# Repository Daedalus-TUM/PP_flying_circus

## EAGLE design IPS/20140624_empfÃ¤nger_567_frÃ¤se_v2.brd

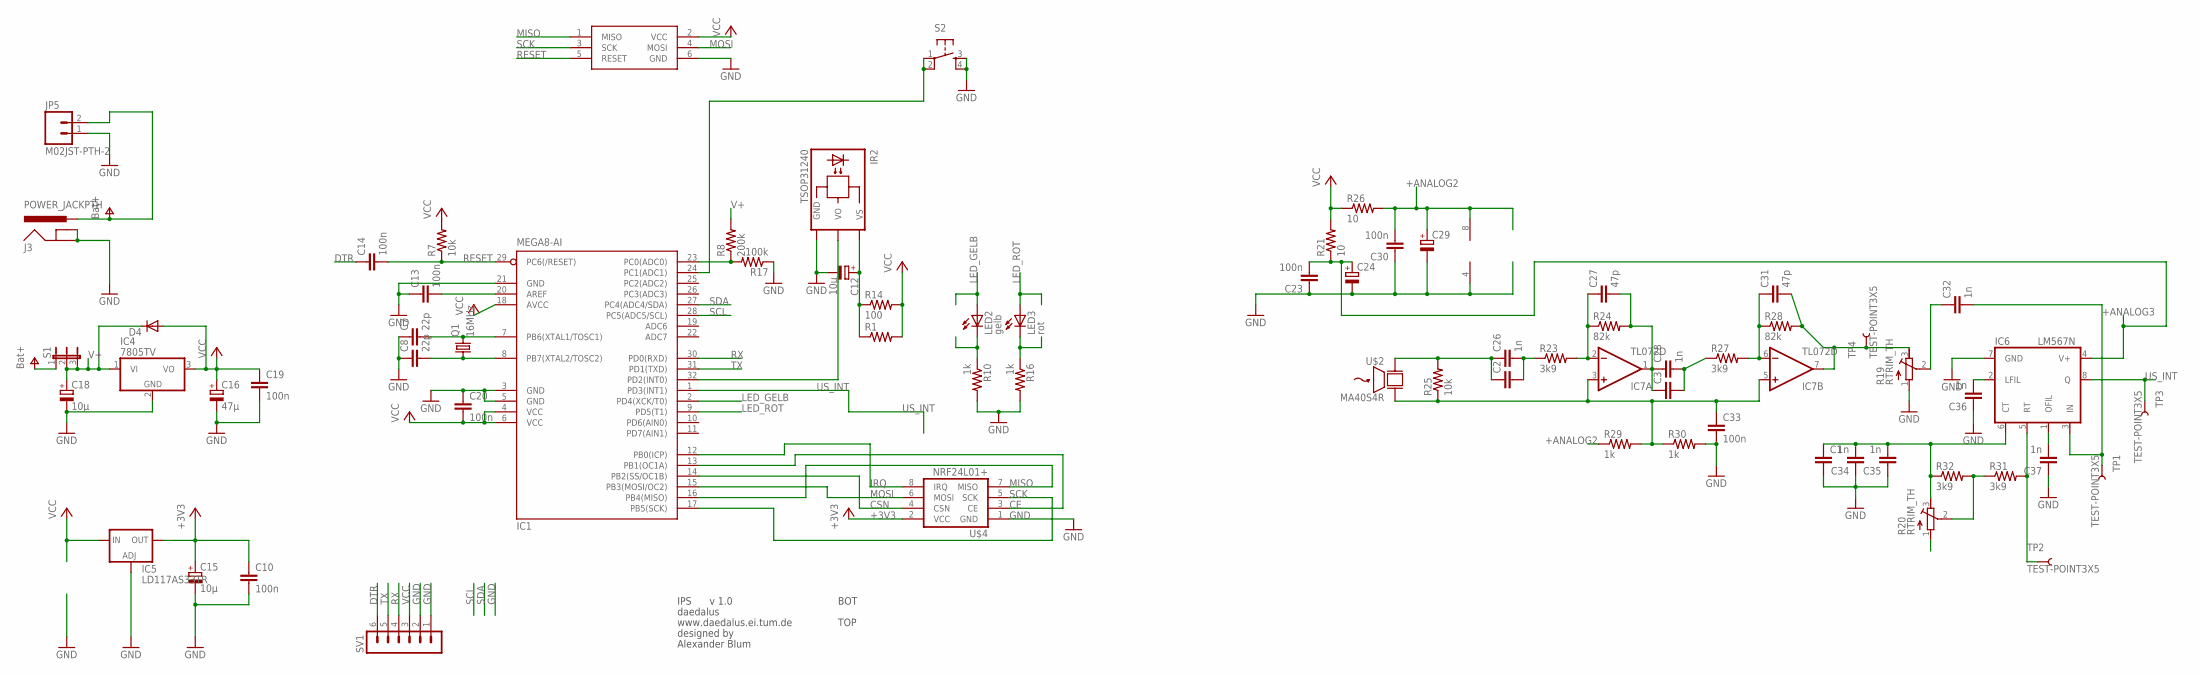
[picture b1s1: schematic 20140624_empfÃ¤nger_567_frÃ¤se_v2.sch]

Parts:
C1, C2, C3: CAP1206; 1206
C7, C8: 22p; 0805
C10, C13, C14, C19, C20, C23, C30, C33: 100n; 0805
C12, C15, C18: 10µ; E2,5-5
C16: 47µ; E2,5-5
C24, C29: CPOL-EUE2.5-5; E2,5-5
C26, C28, C32, C34, C35, C36, C37: 1n; 0805
C27, C31: 47p; 0805
D4: DIODE-MINIMELF; MINIMELF
IC1: MEGA8-AI; TQFP32-08
IC4: 7805TV; TO220V
IC5: LD117AS33TR; SOT223
IC6: LM567N; DIL08
IC7: TL072D; SO08
IR2: TSOP31240
J3: POWER_JACKPTH; POWER_JACK_PTH
JP5: M02JST-PTH-2; JST-2-PTH
LED2: gelb; LED5MM
LED3: rot; LED5MM
Q1: 16MHz; HC49/S
R1: RESISTOR1206; 1206
R7, R25: 10k; 0805
R8: 200k; 0805
R10, R16, R29, R30: 1k; 0805
R14: 100; 0805
R17: 100k; 0805
R19, R20: RTRIM_TH
R21, R26: 10; 0805
R23, R27, R31, R32: 3k9; 0805
R24, R28: 82k; 0805
S1: JP2E; JP2
S2: TAC_SWITCHPTH; TACTILE-PTH
SV1: MA06-1
TP1, TP2, TP3, TP4: TEST-POINT3X5; PAD.03X.05
U$2: MA40S4R; MUS40
U$3: ISP_HEADER
U$4: NRF24L01+; NRF24

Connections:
+3V3: C10.1, C15.+, IC5.4 (OUT), U$4.2 (VCC)
+ANALOG2: C29.+, C30.2, IC7.8 (V+), R26.2, R29.1
+ANALOG3: C23.2, C24.+, IC6.4 (V+), R21.1
BAT+: J3.PWR, JP5.2, S1.1
CE: IC1.13 (PB1(OC1A)), U$4.3 (CE)
CSN: IC1.14 (PB2(SS/OC1B)), U$4.4 (CSN)
DTR: C14.1, SV1.6
GND: C1.2, C7.1, C8.1, C10.2, C12.-, C13.1, C15.-, C16.-, C18.-, C19.2, C20.1, C23.1, C24.-, C29.-, C30.1, C33.2, C34.1, C35.1, C36.1, C37.1, IC1.3 (GND), IC1.5 (GND), IC1.21 (GND), IC4.2 (GND), IC5.1 (ADJ), IC6.7 (GND), IC7.4 (V-), IR2.GND, J3.GND, J3.GNDBREAK, JP5.1, R10.2, R16.2, R17.1, R19.1 (E), R30.2, S2.3, S2.4, SV1.1, SV1.2, U$3.6 (GND), U$4.1 (GND)
IRQ: IC1.12 (PB0(ICP)), U$4.8 (IRQ)
LED_GELB: IC1.2 (PD4(XCK/T0)), LED2.A
LED_ROT: IC1.9 (PD5(T1)), LED3.A
MISO: IC1.16 (PB4(MISO)), U$3.1 (MISO), U$4.7 (MISO)
MOSI: IC1.15 (PB3(MOSI/OC2)), U$3.4 (MOSI), U$4.6 (MOSI)
unnamed: C7.2, IC1.7 (PB6(XTAL1/TOSC1)), Q1.2
unnamed: C12.+, IR2.VS, R1.1, R14.1
unnamed: C8.2, IC1.8 (PB7(XTAL2/TOSC2)), Q1.1
unnamed: IC1.23 (PC0(ADC0)), R8.1, R17.2
unnamed: IC1.32 (PD2(INT0)), IR2.VO
unnamed: R20.2 (S), R31.1, R32.2
unnamed: C13.2, IC1.20 (AREF)
unnamed: LED2.K (C), R10.1
unnamed: LED3.K (C), R16.1
unnamed: C2.2, C26.2, R23.1
unnamed: C27.1, IC7.2 (-IN), R23.2, R24.1
unnamed: C3.1, C27.2, C28.1, IC7.1 (OUT), R24.2
unnamed: C3.2, C28.2, R27.1
unnamed: C2.1, C26.1, R25.2, U$2.2
unnamed: IC6.5 (RT), R31.2, TP2.P$1
unnamed: C33.1, IC7.3 (+IN), IC7.5 (+IN), R25.1, R29.2, R30.1, U$2.1
unnamed: IC1.24 (PC1(ADC1)), S2.1, S2.2
unnamed: C31.1, IC7.6 (-IN), R27.2, R28.1
unnamed: C1.1, C34.2, C35.2, IC6.6 (CT), R20.3 (A), R32.1
unnamed: C31.2, IC7.7 (OUT), R19.3 (A), R28.2, TP4.P$1
unnamed: C32.1, R19.2 (S)
unnamed: C32.2, IC6.3 (IN), TP1.P$1
unnamed: C37.2, IC6.1 (OFIL)
unnamed: C36.2, IC6.2 (LFIL)
RESET: C14.2, IC1.29 (PC6(/RESET)), R7.1, U$3.5 (RESET)
RX: IC1.30 (PD0(RXD)), SV1.4
SCK: IC1.17 (PB5(SCK)), U$3.3 (SCK), U$4.5 (SCK)
SCL: IC1.28 (PC5(ADC5/SCL))
SDA: IC1.27 (PC4(ADC4/SDA))
TX: IC1.31 (PD1(TXD)), SV1.5
US_INT: IC1.1 (PD3(INT1)), IC6.8 (Q), TP3.P$1
V+: C18.+, D4.C, IC4.1 (VI), R8.2, S1.2, S1.3
VCC: C16.+, C19.1, C20.2, D4.A, IC1.4 (VCC), IC1.6 (VCC), IC1.18 (AVCC), IC4.3 (VO), IC5.3 (IN), R1.2, R7.2, R14.2, R21.2, R26.1, SV1.3, U$3.2 (VCC)

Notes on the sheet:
IPS
v 1.0
daedalus
www.daedalus.ei.tum.de
designed by
Alexander Blum
BOT
TOP

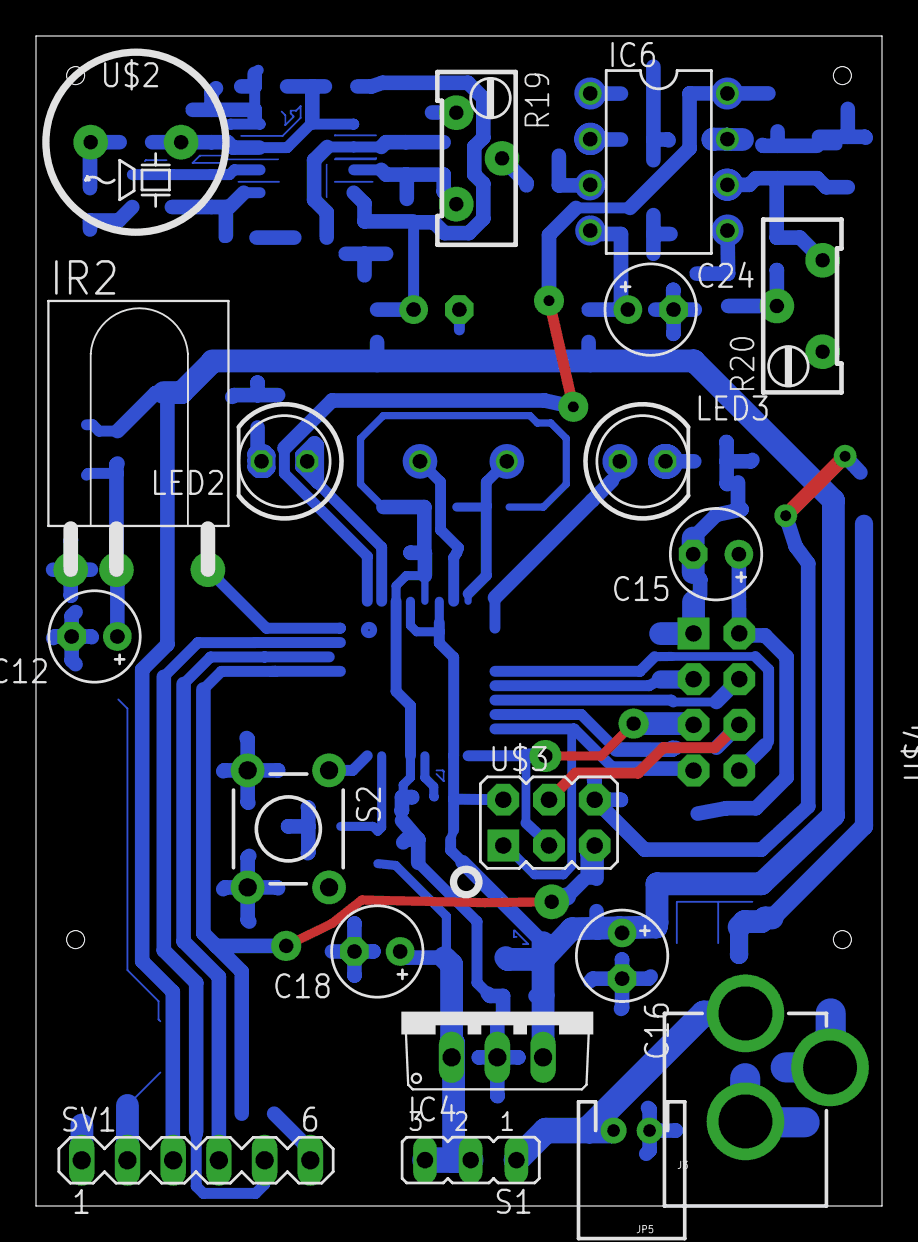
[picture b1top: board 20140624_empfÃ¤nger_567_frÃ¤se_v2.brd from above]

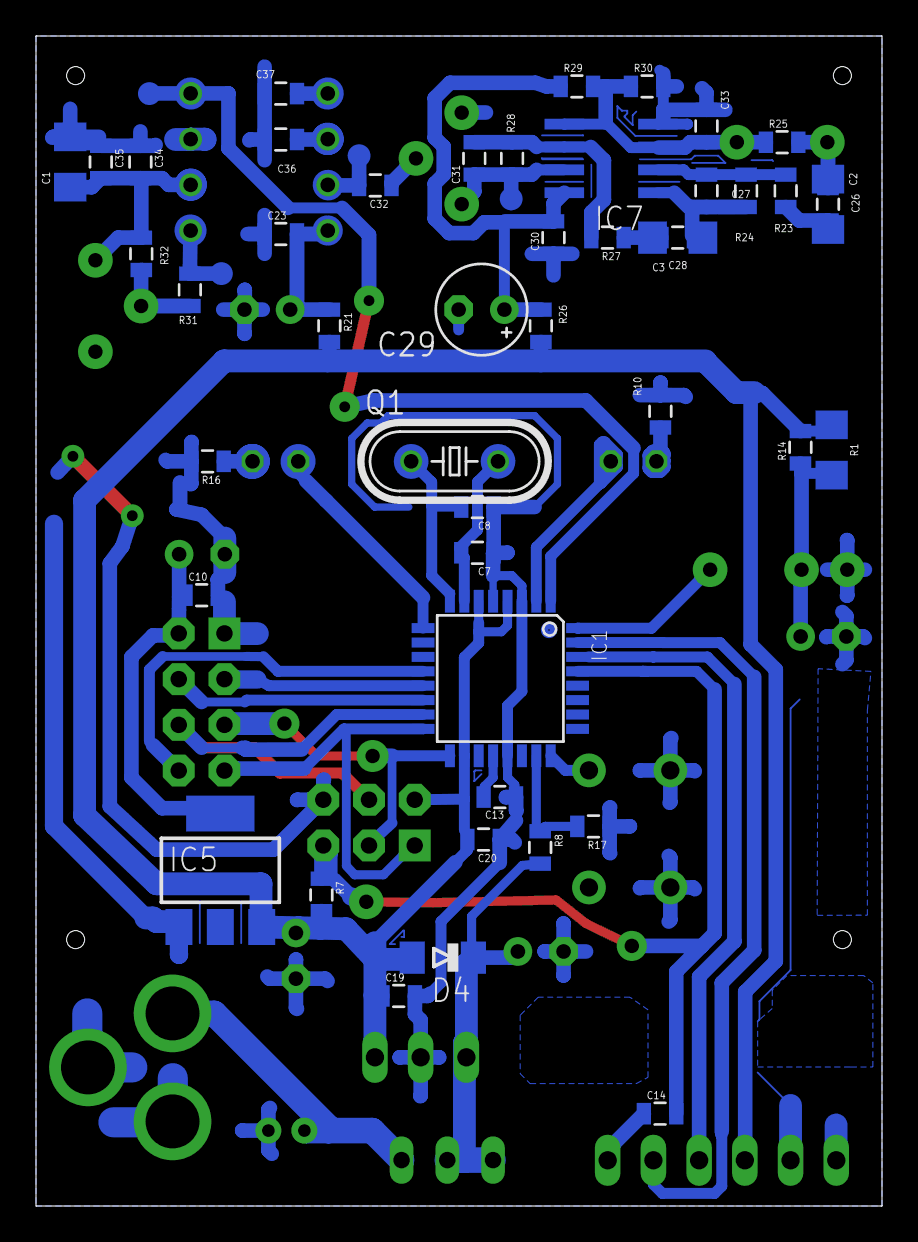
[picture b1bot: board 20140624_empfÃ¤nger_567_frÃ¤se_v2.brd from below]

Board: 2 copper layers, 47.0 x 65.0 mm, 70 parts (50 on the bottom side), 44 nets.

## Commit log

2014-04-26 upload
2014-05-20 funktest
2014-05-22 update Funk
2014-05-23 update Funkverbindung
2014-05-26 upload dropbox
2014-05-28 Create Optimierung
2014-06-01 upload funk doku
2014-06-12 arduino
2014-06-12 team.py

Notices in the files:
parts and their libraries:
SparkFun-Connectors: Licensing: Creative Commons ShareAlike 4.0 International - https://creativecommons.org/licenses/by-sa/4.0
